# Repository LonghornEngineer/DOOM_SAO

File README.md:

### DOOM Shitty Add On Features
***
**Add on for conference badges that features a LCD Screen and DOOM Guy.**

The DOOM Shitty Add On (DOOM SAO) is an add on for conference badges that implement the [V1.69bis standard](https://hackaday.com/2019/03/20/introducing-the-shitty-add-on-v1-69bis-standard/) for SAO devices. Additionally, it has provisions to be a full on development platform for the ATSAMD21G18A microcontroller. The MCU and preinstalled bootloader are also Arduino compatible to aid in the ease of hardware and firmware hacking. This document will explain the feature set and how to interface with the DOOM SAO to bring out its full potential.

## Full Feature Set
* Arduino Compatible MCU ATSAMD21G18A
* All unused I/O from the MCU is accessible
* Full implementation of the [V1.69bis standard](https://hackaday.com/2019/03/20/introducing-the-shitty-add-on-v1-69bis-standard/)
* Auto mode for DOOM Guy for badges that are not DOOM SAO compatible
* Serial Terminal accessible through the USB Type-C connector
* Passive Hardware Bus Sniffing
* User defined section for adding your own code
* High DPI ST7789 1.3" 240x240 LCD Screen
* USB Type-C configured for USB 2.0 (REVERSIBLE)

## Interfacing with the DOOM SAO via Serial UART

Connection Settings: 9600/8/N/1

Ensure your terminal terminates with Carriage Return (The Arduino Serial Monitor defaults to New Line. This is wrong)

Press 'X' to start the interactive menu.

Press 1..6 to select sub-menu options.

Press 'Q' within any sub-menu to quit to the main menu.

Menu Options:

1 - DOOM Guy Interface Mode
This allows you to modify the EEPROM directly to dynamically control the animations and SAO behavior.

2 - DOOM Guy Bus Sniffer Mode
This is a filtered view of the DOOM Guy's I2C traffic. It's a poor man's logic analyzer, decoded for SAO interpretation.

3 - I2C Bus Sniffer Mode
This allows you to monitor the entire I2C bus. If a host has more than one SAO port you can see what magic bytes and data other SAO's are transmitting in addtion to what the badge is using on I2C. It's a poor man's logic analyzer, decoded in general, for seeing I2C NACK, ACK, Reads, and Writes.

4 - Serial UART Sniffer Mode
This allows you to passively man in the middle another embedded system's serial UART line. 
Connect the source's serial TX to the SAO RX Pin PB23.
Connect the target's serial RX to the SAO TX Pin PB22.
Choose the appropriate baud rate and byte translation (ASCII or DEC).

5 - Custom  Application Mode
This is the area for YOU to add your own code.

6 - EEPROM Persistance Mode
This allows you to save changes made to the EEPROM, which by default reset on power cycle.

6 - BADGE SAO Airplane Mode
This allows you to ignore all logical control of the host badge. In minor cases, a badge may have a component which uses the same address (0x50) as our SAO, which will result in unexpected behavior. This is known to be the case with Team Ides DaBomb! Badge. In this case, enable persistance, enable airplane mode, then disable persistance so the SAO can still operate in a standalone mode. Not doing so will require reflashing of the SAO with the Arduino IDE.

## Interfacing with the DOOM SAO via I2C

The DOOM SAO implements the [V1.69bis standard](https://hackaday.com/2019/03/20/introducing-the-shitty-add-on-v1-69bis-standard/) for SAO devices and follows the [AND!XOR SAO Reference Design](https://github.com/ANDnXOR/sao-reference-designs). What this means is that using the I2C interface and GPIO pins of the V1.69bis standard users will be able to control how DOOM Guy acts and behaves.

The I2C address for DOOM SAO is 0x50. This is the standard address for the I2C AT24C32 EEPROM. Over the I2C interface, DOOM SAO acts like a simulated EEPROM. Only single byte reads and writes are supported. Attempting to do multi byte reads or writes are not implemented at this time. For identification purposes the first 3 address locations are used. See the [AND!XOR SAO Reference Design](https://github.com/ANDnXOR/sao-reference-designs) for more information. Below is the EEPROM address structure. 

| 0		| 1		| 2 	| 3...n	|
|:-:	|:-:	|:-:	|:-:	|
| 0x1B	| 0x05	| 0x01	| Data	|

* Address 0 is the DC Year. Use 0x1B for DC27.
* Address 1 is my Maker ID which is a unique identifier for SAO maker, I chose 0x05 at random for my maker ID. I do not know if there is a list of these ¯\_(ツ)_/¯.
* Address 2 is the SAO Type ID which is a unique identifier for the SAO. DOOM SAO is my only SAO so it is 0x01. 
* Addresss 3..n is where you can write stuff to the SAO!

First 3 addresses are protected and can not be overwritten unless you change them in the firmware and reflash the MCU.

### EEPROM Addresses

| Address	| Content	| Default Value	| Protected?	|
|:-:		|:-:		|:-:			|:-:			|
| 0x00		| DC Year	| 0x1B			| Yes			|
| 0x01		| Maker ID	| 0x05			| Yes			|
| 0x02		| SAO ID	| 0x01			| Yes			|
| 0x03		| AutoMode	| 0x01			| No			|
| 0x04		| Health	| 0x64			| No			|
| 0x05		| Anger	| 0x00			| No			|

### EEPROM functionality (quirks to note) 

Write functions to the DOOM SAO will always ACK regardless if you where successful or not in writing to that address location.
Reading data locations that do not exist will return with data 0x00. 

### What is Auto Mode?

When first booted up, DOOM SAO defaults to an auto mode. In this mode, Doom Guy looks left and right in an alternating manner with no control from the Badge. Writing a 0x00 value to this address disables auto mode and allows the GPIO to control DOOM Guy. With auto mode disabled, GPIO 1 makes DOOM Guy look left and GPIO 2 makes DOOM Guy look right. Truth table below.

| GPIO 1	| GPIO 2	| What Happens?			|
|:-:		|:-:		|:-:					|
| 0			| 0			| DG Looks Forward		|
| 1			| 0			| DG Looks Left			|
| 0			| 1			| DG Looks Right		|
| 1			| 1			| DG Looks Backwards	|

### What is Health?

The more "damage" Doom Guy takes the more beat up he becomes. Writing a value under 0x64 (100HP) will make Doom Guy look more bloody like he has been punched by a couple of demons. 

### What is Anger?

When Doom Guy gets pissed he gets pissed. Writing a 0x01 value to this location will seriously piss Doom Guy off. This must be his special spot. 

***
**License Information**

PROPRIETARY AND CONFIDENTIAL UNTIL AUGUST 11th, 2019 then,
Licensed under the Apache License, Version 2.0 (the "License");
you may not use this file except in compliance with the License.
You may obtain a copy of the License at
 
http://www.apache.org/licenses/LICENSE-2.0
 
Unless required by applicable law or agreed to in writing, software
distributed under the License is distributed on an "AS IS" BASIS,
WITHOUT WARRANTIES OR CONDITIONS OF ANY KIND, either express or implied.
See the License for the specific language governing permissions and
limitations under the License.
 
***

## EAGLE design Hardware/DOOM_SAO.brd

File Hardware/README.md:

### DOOM Shitty Add On Hardware
***
**Add on for conference badges that features a LCD Screen and DOOM Guy.**

PCB was designed in AutoDesk Eagle V9.3+

## Hardware Specifications
* Arduino Compatible MCU ATSAMD21G18A
* Full implementation of the [V1.69bis standard](https://hackaday.com/2019/03/20/introducing-the-shitty-add-on-v1-69bis-standard/)
* High DPI ST7789 1.3" 240x240 LCD Screen
* USB Type-C configured for USB 2.0 (REVERSIBLE)
* TPS2113ADRBR Power Mux to prevent voltage back feed onto badge when USB power applied
* Tag Connect for ATMEL SWD Programming
* Unused GPIO from MCU broken out to headers
* Possibly the only 4 Layer SAO

## PCB Layers
1. Component mounting and signals
2. Ground
3. +3.3V
4. GPIO Breakout signals

## Schematic

## Board Layout

## PCB Render

***
**License Information**

This project is under the [Creative Commons Attribution-ShareAlike 4.0 International License](LICENSE.md). These files are provided with no warranty and should be used at your own risk. 

***

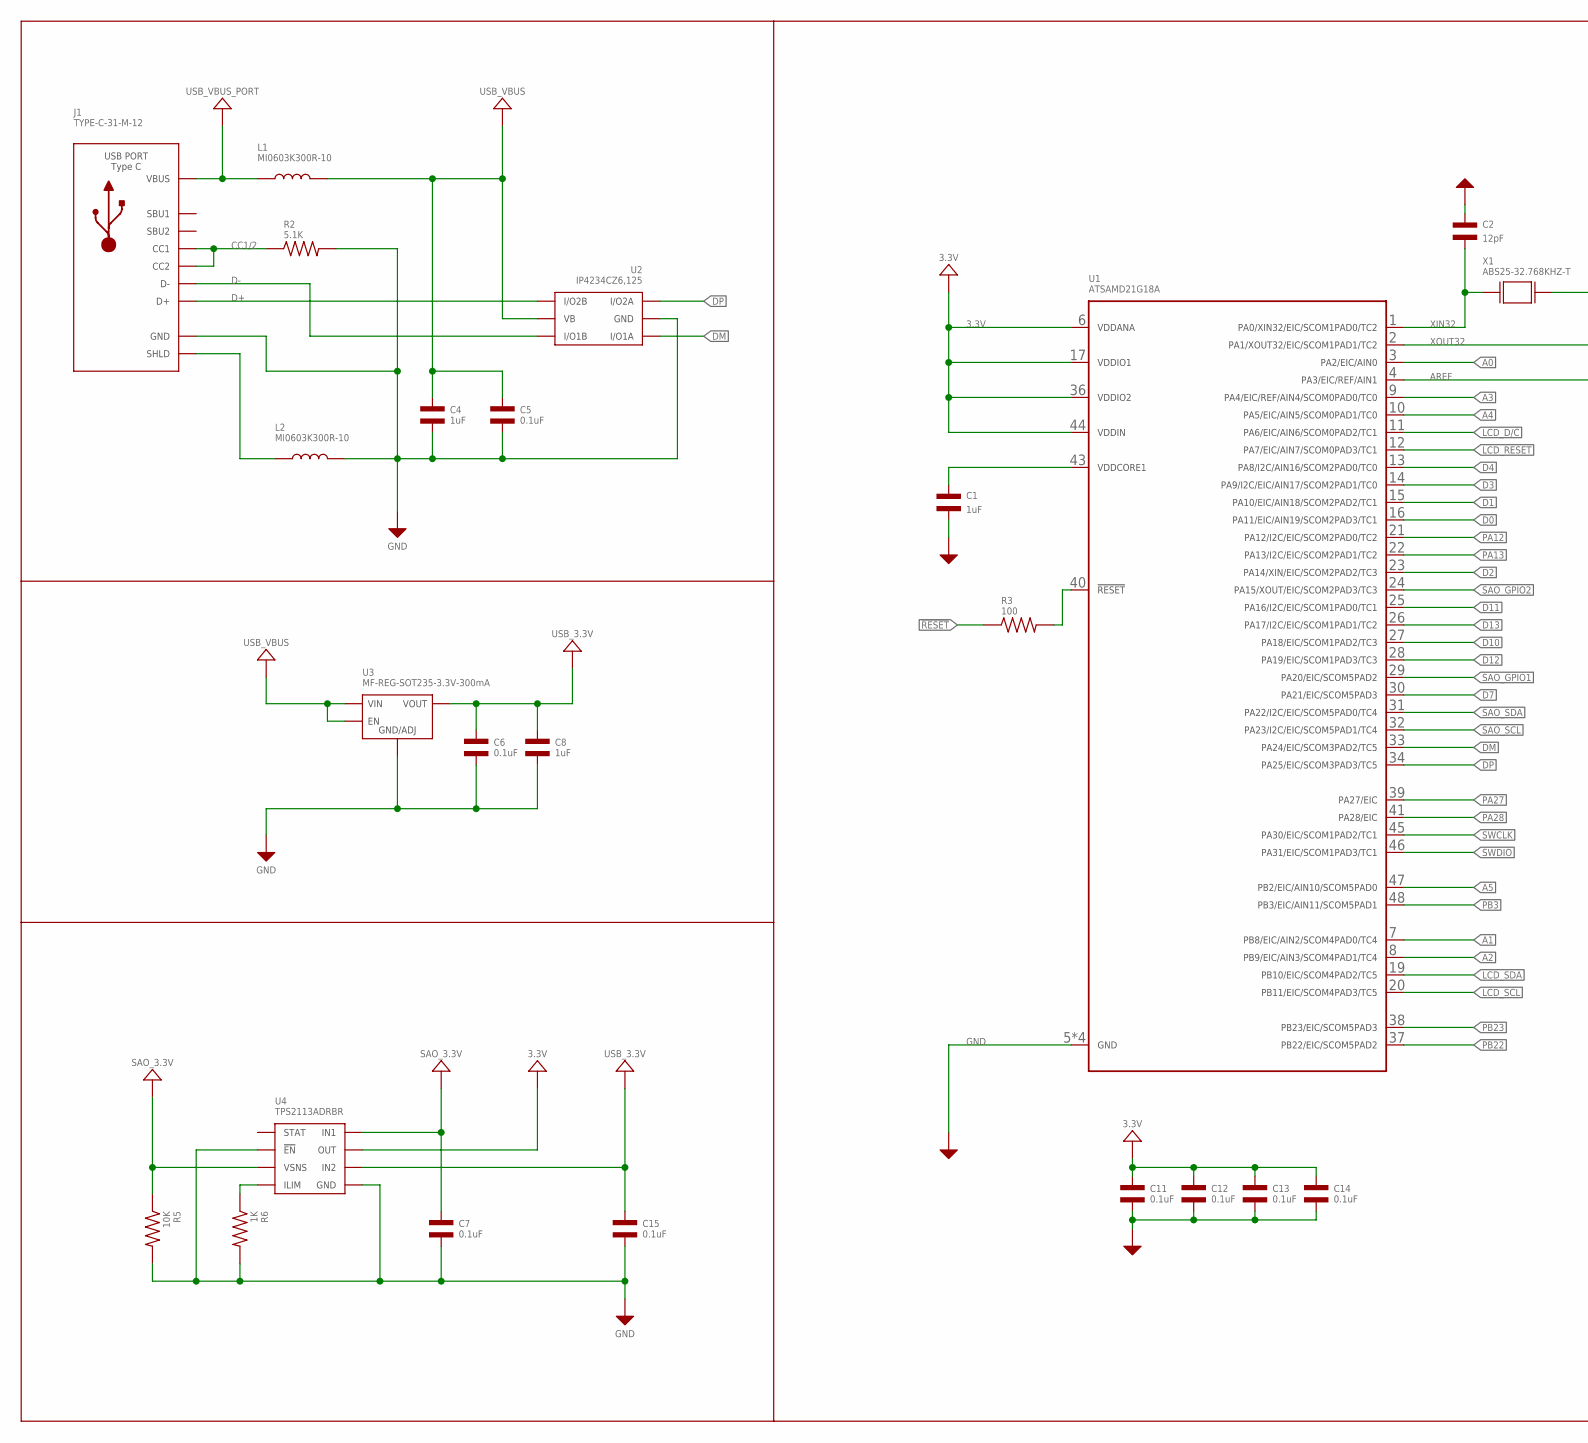
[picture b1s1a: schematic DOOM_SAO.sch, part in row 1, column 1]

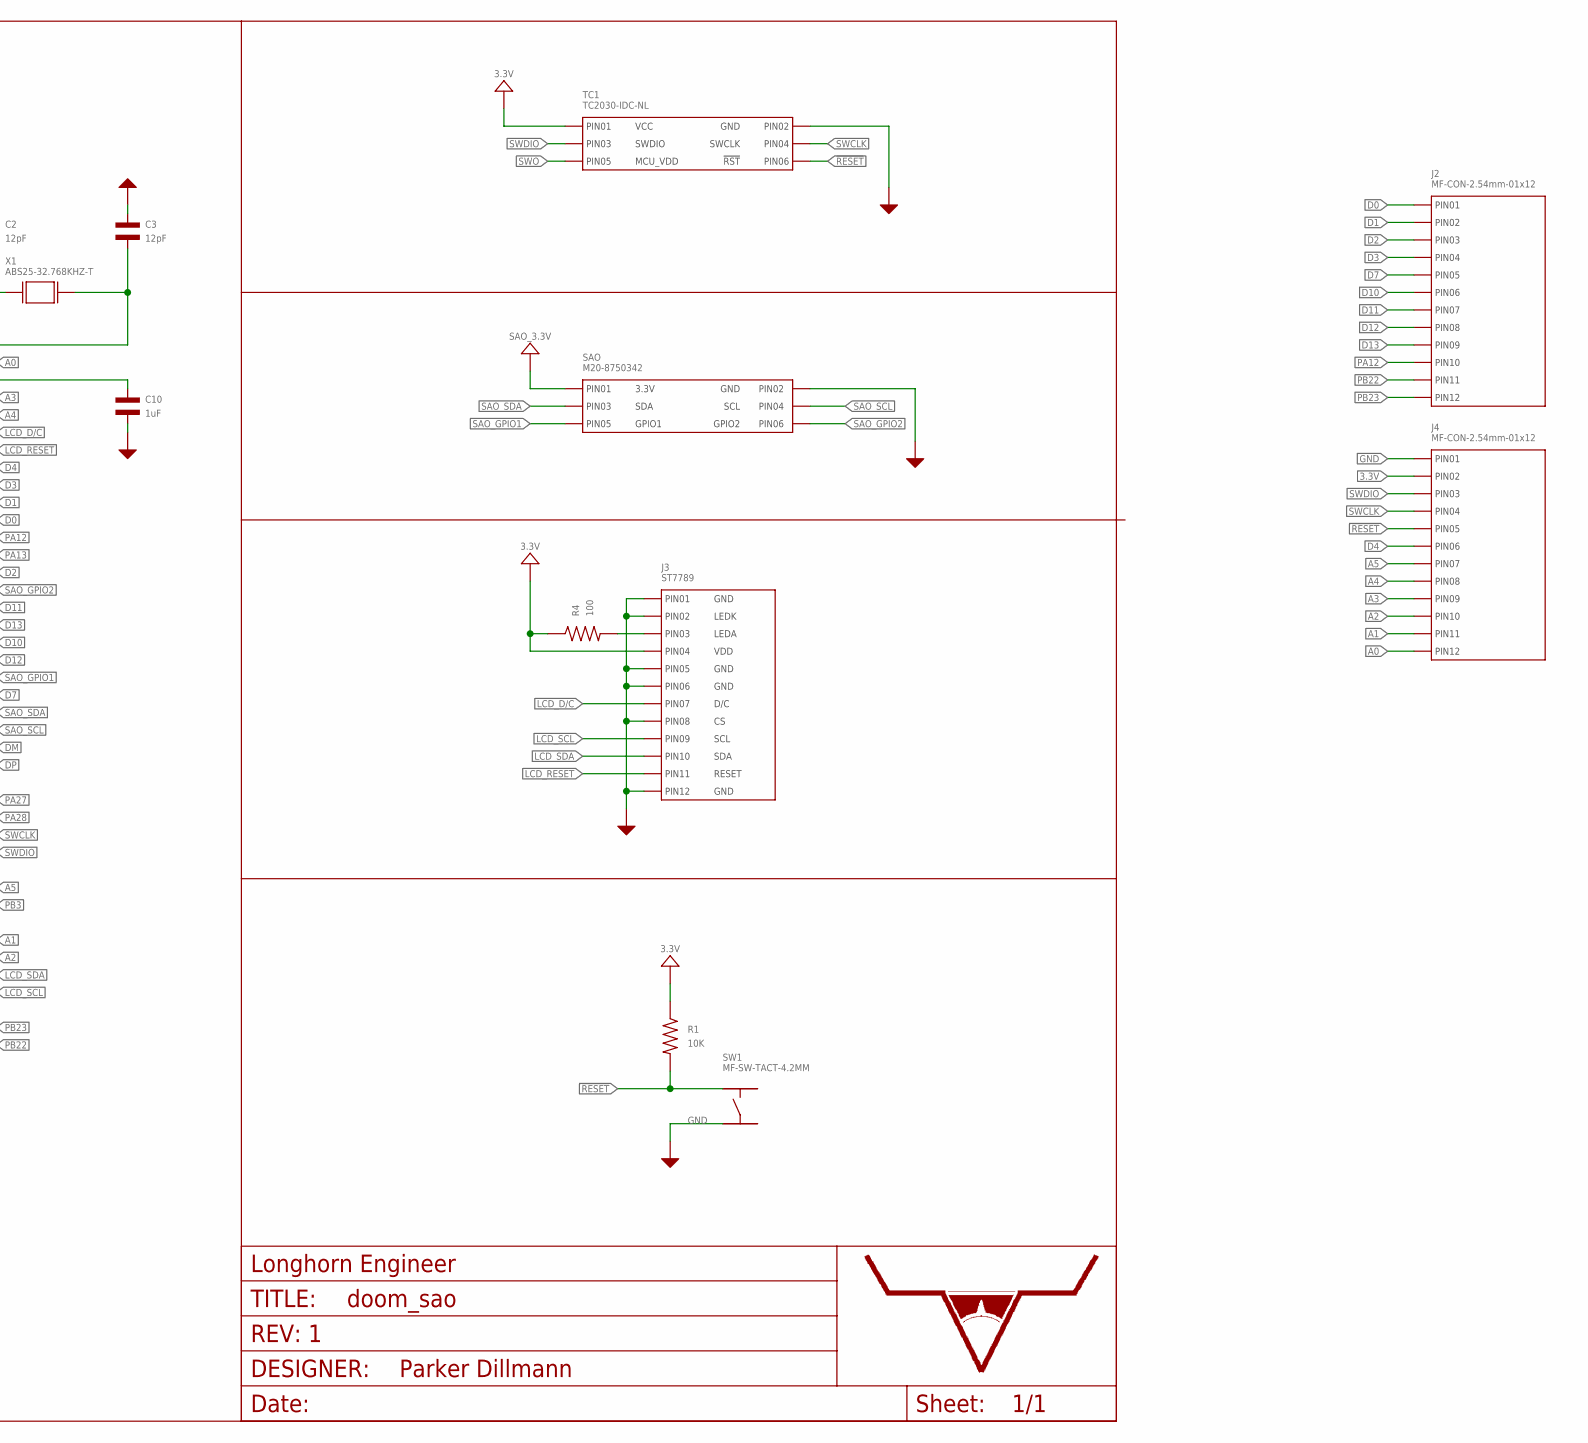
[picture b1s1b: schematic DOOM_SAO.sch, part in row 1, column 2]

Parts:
C1, C4, C8, C10: 1uF; C0402; MPN MF-CAP-0402-1uF
C2, C3: 12pF; C0402; MPN CC0402JRNPO9BN120
C5, C6, C7, C11, C12, C13, C14, C15: 0.1uF; C0402; MPN MF-CAP-0402-0.1uF
J1: TYPE-C-31-M-12; MPN TYPE-C-31-M-12
J2, J4: MF-CON-2.54mm-01x12; PTH_2.54MM_01X12
J3: ST7789; ST7789_CONNECTOR
L1, L2: MI0603K300R-10; L0603; MPN MI0603K300R-10
R1, R5: 10K; R0402; MPN MF-RES-0402-10K
R2: 5.1K; R0402; MPN ERJ-2RHD5101X
R3, R4: 100; R0402; MPN MF-RES-0402-100
R6: 1K; R0402; MPN MF-RES-0402-1K
SAO: M20-8750342; MPN M20-8750342
SW1: MF-SW-TACT-4.2MM; TACT4.2MM
TC1: TC2030-IDC-NL
U1: ATSAMD21G18A; ATSAMD21G18A_TQFP-48; MPN ATSAMD21G18A-AU
U2: IP4234CZ6,125; IP4234CZ6_SOT-457-6; MPN IP4234CZ6,125
U3: MF-REG-SOT235-3.3V-300mA; SOT-23-5
U4: TPS2113ADRBR; TPS211X_SON-8
U$8: LHE_FRAME
X1: ABS25-32.768KHZ-T; ABS25_SERIES; MPN ABS25-32.768KHZ-T

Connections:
3.3V: C11.P$1, C12.P$1, C13.P$1, C14.P$1, J3.P$4 (4), J4.P$2 (PIN2), R1.P$1, R4.P$1, TC1.P$1 (PIN1), U1.6 (VDDANA), U1.17 (VDDIO1), U1.36 (VDDIO2), U1.44 (VDDIN), U4.7 (OUT)
!RESET: J4.P$5 (PIN5), R1.P$2, R3.P$1, SW1.P$1, TC1.P$6 (PIN6)
A0: J4.P$12 (PIN12), U1.3 (PA2/EIC/AIN0)
A1: J4.P$11 (PIN11), U1.7 (PB8/EIC/AIN2/SCOM4PAD0/TC4)
A2: J4.P$10 (PIN10), U1.8 (PB9/EIC/AIN3/SCOM4PAD1/TC4)
A3: J4.P$9 (PIN9), U1.9 (PA4/EIC/REF/AIN4/SCOM0PAD0/TC0)
A4: J4.P$8 (PIN8), U1.10 (PA5/EIC/AIN5/SCOM0PAD1/TC0)
A5: J4.P$7 (PIN7), U1.47 (PB2/EIC/AIN10/SCOM5PAD0)
AREF: C10.P$1, U1.4 (PA3/EIC/REF/AIN1)
BK_LIGHT: J3.P$3 (3), R4.P$2
CC1/2: J1.A5 (CC1), J1.B5 (CC2), R2.P$1
D0: J2.P$1 (PIN1), U1.16 (PA11/EIC/AIN19/SCOM2PAD3/TC1)
D1: J2.P$2 (PIN2), U1.15 (PA10/EIC/AIN18/SCOM2PAD2/TC1)
D2: J2.P$3 (PIN3), U1.23 (PA14/XIN/EIC/SCOM2PAD2/TC3)
D3: J2.P$4 (PIN4), U1.14 (PA9/I2C/EIC/AIN17/SCOM2PAD1/TC0)
D4: J4.P$6 (PIN6), U1.13 (PA8/I2C/AIN16/SCOM2PAD0/TC0)
D7: J2.P$5 (PIN5), U1.30 (PA21/EIC/SCOM5PAD3)
D10: J2.P$6 (PIN6), U1.27 (PA18/EIC/SCOM1PAD2/TC3)
D11: J2.P$7 (PIN7), U1.25 (PA16/I2C/EIC/SCOM1PAD0/TC1)
D12: J2.P$8 (PIN8), U1.28 (PA19/EIC/SCOM1PAD3/TC3)
D13: J2.P$9 (PIN9), U1.26 (PA17/I2C/EIC/SCOM1PAD1/TC2)
D+: J1.A6 (D+), J1.B6 (D+), U2.4 (I/O2B)
D-: J1.A7 (D-), J1.B7 (D-), U2.3 (I/O1B)
DM: U1.33 (PA24/EIC/SCOM3PAD2/TC5), U2.1 (I/O1A)
DP: U1.34 (PA25/EIC/SCOM3PAD3/TC5), U2.6 (I/O2A)
GND: C1.P$2, C2.P$1, C3.P$1, C4.P$2, C5.P$2, C6.P$2, C7.P$2, C8.P$2, C10.P$2, C11.P$2, C12.P$2, C13.P$2, C14.P$2, C15.P$2, J1.A1/B12 (GND), J1.B1/A12 (GND), J3.P$1 (1), J3.P$2 (2), J3.P$5 (5), J3.P$6 (6), J3.P$8 (8), J3.P$12 (12), J4.P$1 (PIN1), L2.P$2, R2.P$2, R5.P$2, R6.P$2, SAO.2 (PIN2), SW1.P$3, TC1.P$2 (PIN2), U1.5 (GND), U1.18 (GND), U1.35 (GND), U1.42 (GND), U2.2 (GND), U3.P$2 (GND/ADJ), U4.2 (!EN), U4.5 (GND), U4.PAD (GND)
LCD_D/C: J3.P$7 (7), U1.11 (PA6/EIC/AIN6/SCOM0PAD2/TC1)
LCD_RESET: J3.P$11 (11), U1.12 (PA7/EIC/AIN7/SCOM0PAD3/TC1)
LCD_SCL: J3.P$9 (9), U1.20 (PB11/EIC/SCOM4PAD3/TC5)
LCD_SDA: J3.P$10 (10), U1.19 (PB10/EIC/SCOM4PAD2/TC5)
PA12: J2.P$10 (PIN10), U1.21 (PA12/I2C/EIC/SCOM2PAD0/TC2)
PA13: U1.22 (PA13/I2C/EIC/SCOM2PAD1/TC2)
PA27: U1.39 (PA27/EIC)
PA28: U1.41 (PA28/EIC)
PB3: U1.48 (PB3/EIC/AIN11/SCOM5PAD1)
PB22: J2.P$11 (PIN11), U1.37 (PB22/EIC/SCOM5PAD2)
PB23: J2.P$12 (PIN12), U1.38 (PB23/EIC/SCOM5PAD3)
RESETLIN: R3.P$2, U1.40 (!RESET)
SAO_3.3V: C7.P$1, R5.P$1, SAO.1 (PIN1), U4.3 (VSNS), U4.8 (IN1)
SAO_GPIO1: SAO.5 (PIN5), U1.29 (PA20/EIC/SCOM5PAD2)
SAO_GPIO2: SAO.6 (PIN6), U1.24 (PA15/XOUT/EIC/SCOM2PAD3/TC3)
SAO_SCL: SAO.4 (PIN4), U1.32 (PA23/I2C/EIC/SCOM5PAD1/TC4)
SAO_SDA: SAO.3 (PIN3), U1.31 (PA22/I2C/EIC/SCOM5PAD0/TC4)
SHLD: J1.MT_B_0 (SHLD), J1.MT_B_1 (SHLD), J1.MT_B_2 (SHLD), J1.MT_B_3 (SHLD), J1.MT_T_0 (SHLD), J1.MT_T_1 (SHLD), J1.MT_T_2 (SHLD), J1.MT_T_3 (SHLD), L2.P$1
SWCLK: J4.P$4 (PIN4), TC1.P$4 (PIN4), U1.45 (PA30/EIC/SCOM1PAD2/TC1)
SWDIO: J4.P$3 (PIN3), TC1.P$3 (PIN3), U1.46 (PA31/EIC/SCOM1PAD3/TC1)
SWO: TC1.P$5 (PIN5)
TPS_ILIM: R6.P$1, U4.4 (ILIM)
USB_3.3V: C6.P$1, C8.P$1, C15.P$1, U3.P$5 (VOUT), U4.6 (IN2)
USB_VBUS: C4.P$1, C5.P$1, L1.P$2, U2.5 (VB), U3.P$1 (VIN), U3.P$3 (EN)
USB_VBUS_PORT: J1.A4/B9 (VBUS), J1.B4/A9 (VBUS), L1.P$1
VDDCORE: C1.P$1, U1.43 (VDDCORE1)
XIN32: C2.P$2, U1.1 (PA0/XIN32/EIC/SCOM1PAD0/TC2), X1.1 (X0)
XOUT32: C3.P$2, U1.2 (PA1/XOUT32/EIC/SCOM1PAD1/TC2), X1.4 (X1)

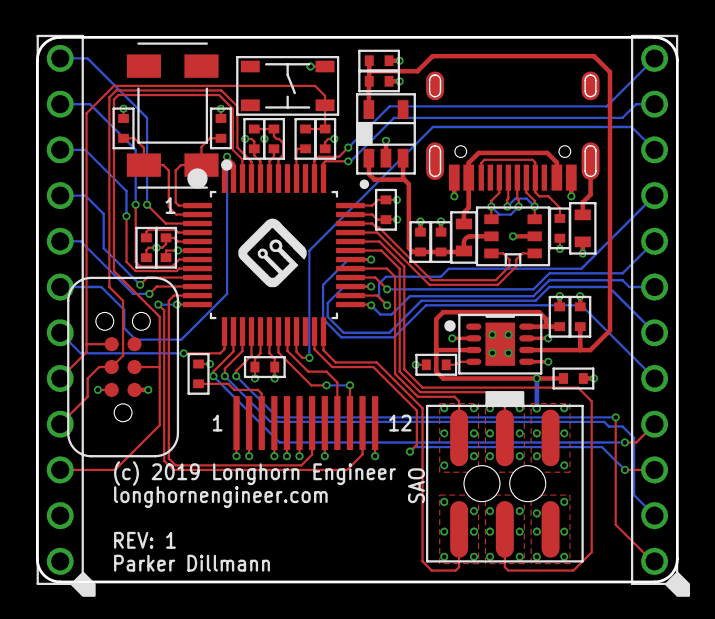
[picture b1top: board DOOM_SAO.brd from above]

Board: 4 copper layers, 35.6 x 30.3 mm, 36 parts (0 on the bottom side), 49 nets.

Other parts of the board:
U$9: MF_LOGO_SMALL

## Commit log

2019-06-17 first REV
2019-06-17 updated copyright year
2019-06-17 Working on adding EEPROM
2019-06-28 Readme for Hardware
2019-07-05 Working on Readmes
2019-07-05 Implemented single byte reads and writes for simulated EEPROM
2019-07-06 Updated README.md with Linux relevant information
2019-07-07 Menu added
2019-07-07 Menu++
2019-07-07 Menu and serial sniffer performance boost
2019-07-08 pushing first draft
2019-07-08 MOAR
2019-07-14 Will single stop work?
2019-07-14 Single Stop and Double Stop working for reads.
2019-07-14 Updated Firmware section of readme
2019-07-14 Updated Readme UUHGAIN
2019-07-14 Updated License Info
2019-07-14 License Update
2019-07-14 License Update (again)
2019-07-14 Software Header License
2019-07-14 Added more DG Faces and Automode implemented
2019-07-14 Added VSCode settings to ignore
2019-07-14 Automode complete! Moved junk to own function to clean up loop.
2019-07-14 BADGE DIRECT CONTROL MODE complete
2019-07-14 Fixing comments
2019-07-14 Menu update and adding Interface mode (WIP)
2019-07-14 Interface Mode (read only, writes coming next)
2019-07-14 Interface Mode EEPROM Writes
2019-07-15 Persistance
2019-07-17 Code cleanup, isolate eeprom write, fix terminal for returns
2019-07-17 I2C Sniffer implemented!
2019-07-17 tweaked menu selection for i2c sniffer
2019-07-17 Updated functionality menu description
2019-07-17 Replace "Doom" with "DOOM"
2019-07-17 Updating Solder Fixture for screens
2019-07-18 I can't spell Carriage
2019-07-18 Updated EEPROM Addresses
2019-07-18 Updated Mode titles
2019-07-18 adding more stuffz
2019-07-18 testing out gif in readme?
2019-07-18 clean up of TBD
2019-07-27 Implemented dealwithit.
2019-07-27 minor change with dealwithit
2019-07-27 Fixing anger and duplicate/incorrect faces.
2019-07-27 Pulling GPIO low in setup.
2019-07-28 Airplane mode to mitigate I2C Address Conflict
    This was discovered due to DaBomb badge LED Driver using same address as our EEPROM

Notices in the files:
parts and their libraries:
PP_Aesthetics: (c) 2019 Longhorn Engineer
